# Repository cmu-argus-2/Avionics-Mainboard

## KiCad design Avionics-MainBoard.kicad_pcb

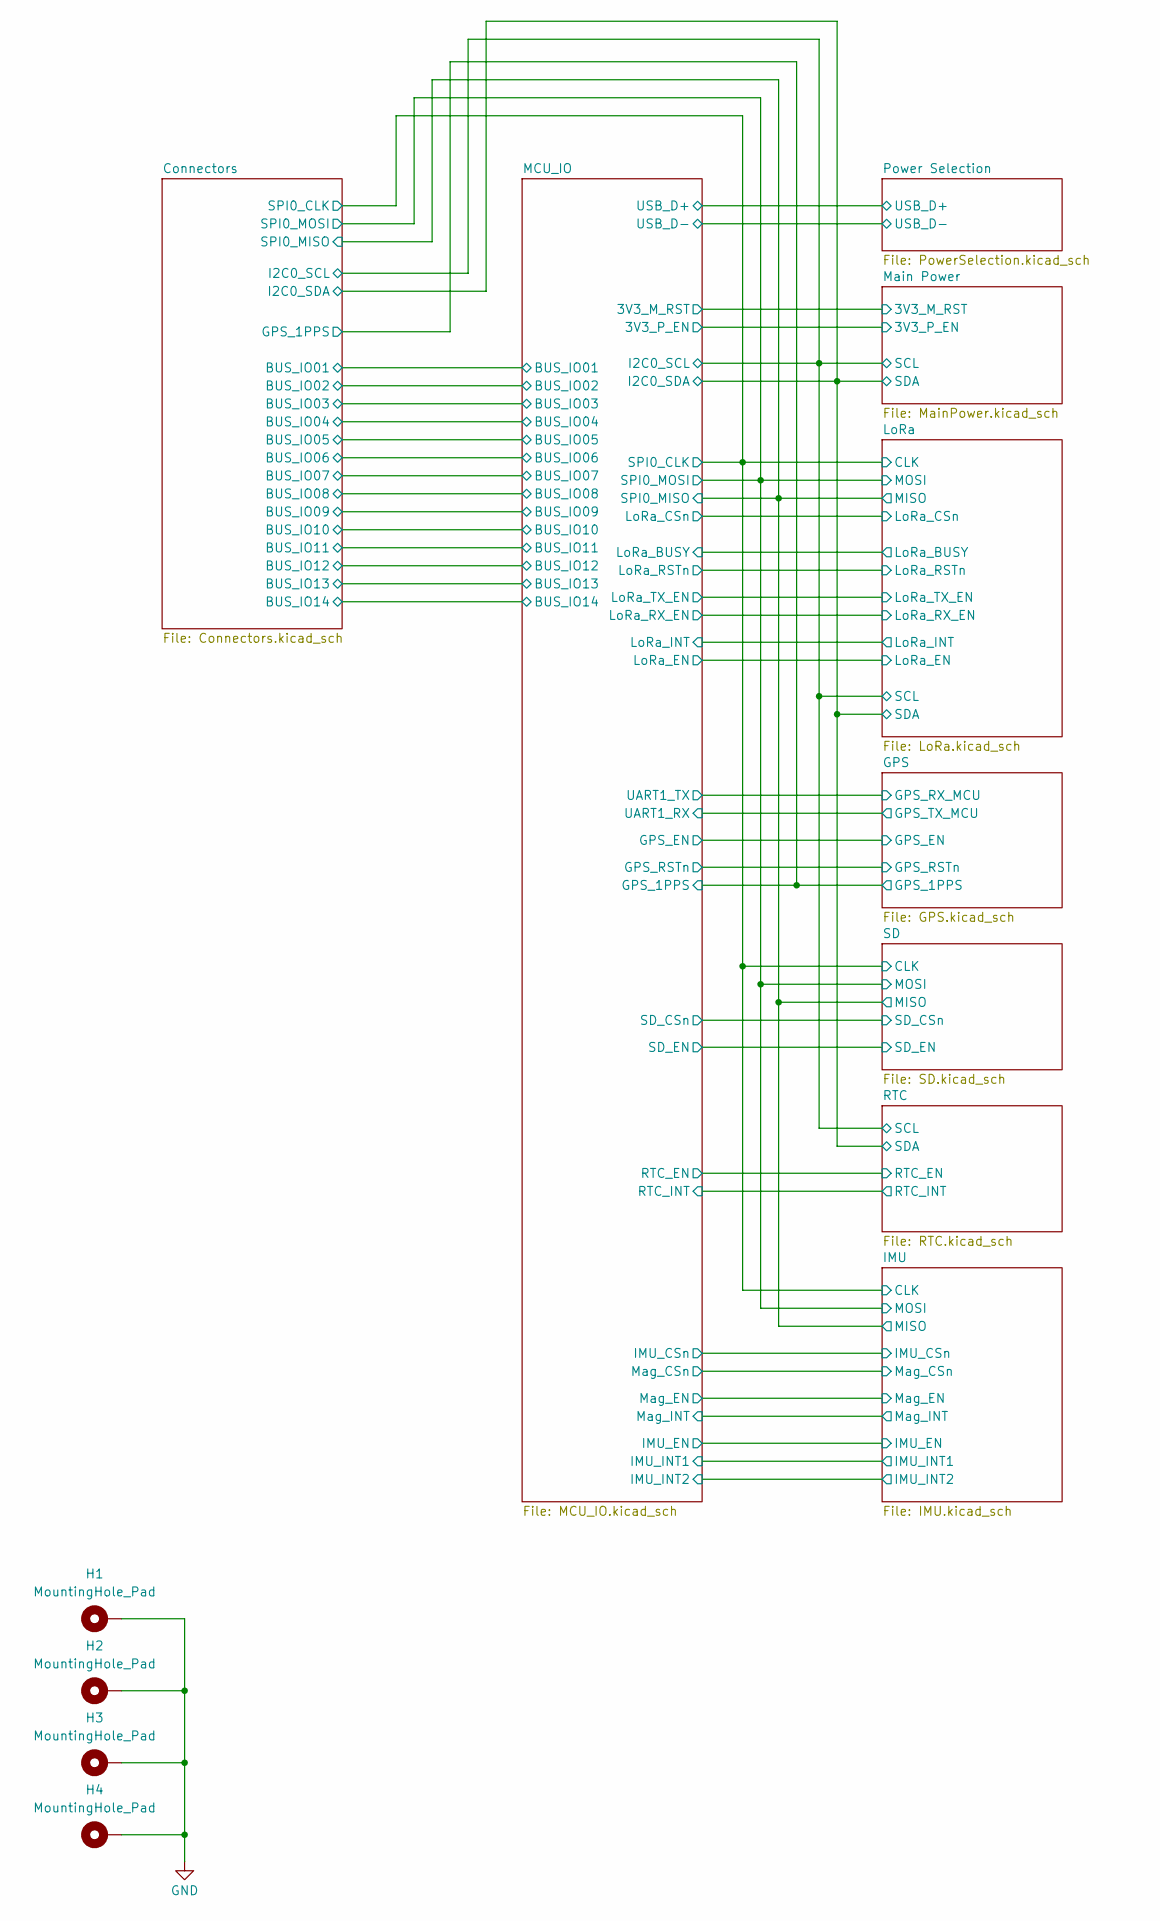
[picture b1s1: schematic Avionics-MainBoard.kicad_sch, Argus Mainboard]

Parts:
H1, H2, H3, H4: MountingHole_Pad; MountingHole_3.2mm_M3_Pad_Via

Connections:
GND: H1.1 (1_1), H2.1 (1_1), H3.1 (1_1), H4.1 (1_1); also elsewhere on the board

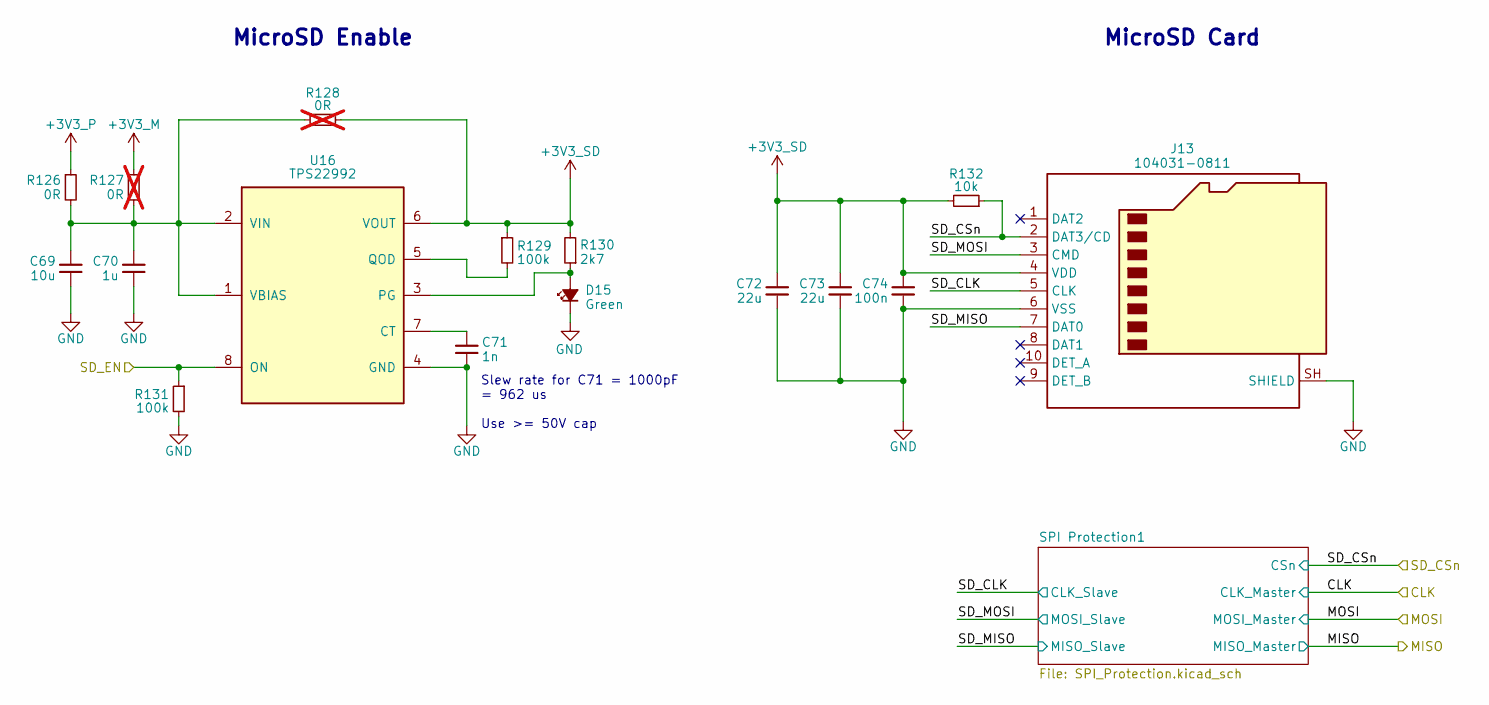
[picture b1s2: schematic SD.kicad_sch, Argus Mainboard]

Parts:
C69: 10u; C_0805_2012Metric; MPN C307348
C70: 1u; C_0603_1608Metric; MPN C307348
C71: 1n; C_0603_1608Metric; MPN C307348
C72, C73: 22u; C_1210_3225Metric
C74: 100n; C_0603_1608Metric; MPN C307348
D15: LED_G_0603_LTST-C190GKT; LED_0603_1608Metric; MPN C2909774
J13: 104031-0811; microSD_HC_Molex_104031-0811; MPN C585350
R126: 0R; R_0603_1608Metric
R127: 0R; R_0603_1608Metric; not fitted
R128: 0R; R_0603_1608Metric; MPN C2479067; not fitted
R129, R131: 100k; R_0603_1608Metric; MPN C2479067
R130: 2k7; R_0603_1608Metric; MPN C237112
R132: 10k; R_0603_1608Metric; MPN C2479067
U16: TPS22992

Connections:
+3V3_M: R127.1; also elsewhere on the board
+3V3_P: R126.1; also elsewhere on the board
+3V3_SD: C72.1, C73.1, C74.1, J13.4 (VDD), R128.1, R129.1, R130.2, R132.2, U16.6 (VOUT)
/MCU_IO/SD_CSn: J13.2 (DAT3/CD), R132.1; also elsewhere on the board
/MCU_IO/SD_EN: R131.1, U16.8 (ON); also elsewhere on the board
/SD/SD_CLK: J13.5 (CLK); also elsewhere on the board
/SD/SD_MISO: J13.7 (DAT0); also elsewhere on the board
/SD/SD_MOSI: J13.3 (CMD); also elsewhere on the board
GND: C69.2, C70.2, C71.2, C72.2, C73.2, C74.2, D15.1 (K), J13.6 (VSS), J13.SH (SHIELD), R131.2, U16.4 (GND); also elsewhere on the board
unnamed: D15.2 (A), R130.1, U16.3 (PG)
unnamed: C71.1, U16.7 (CT)
unnamed: R129.2, U16.5 (QOD)
unnamed: C69.1, C70.1, R126.2, R127.2, R128.2, U16.1 (VBIAS), U16.2 (VIN)

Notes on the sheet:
Slew rate for C71 = 1000pF = 962 us Use >= 50V cap
MicroSD Enable
MicroSD Card

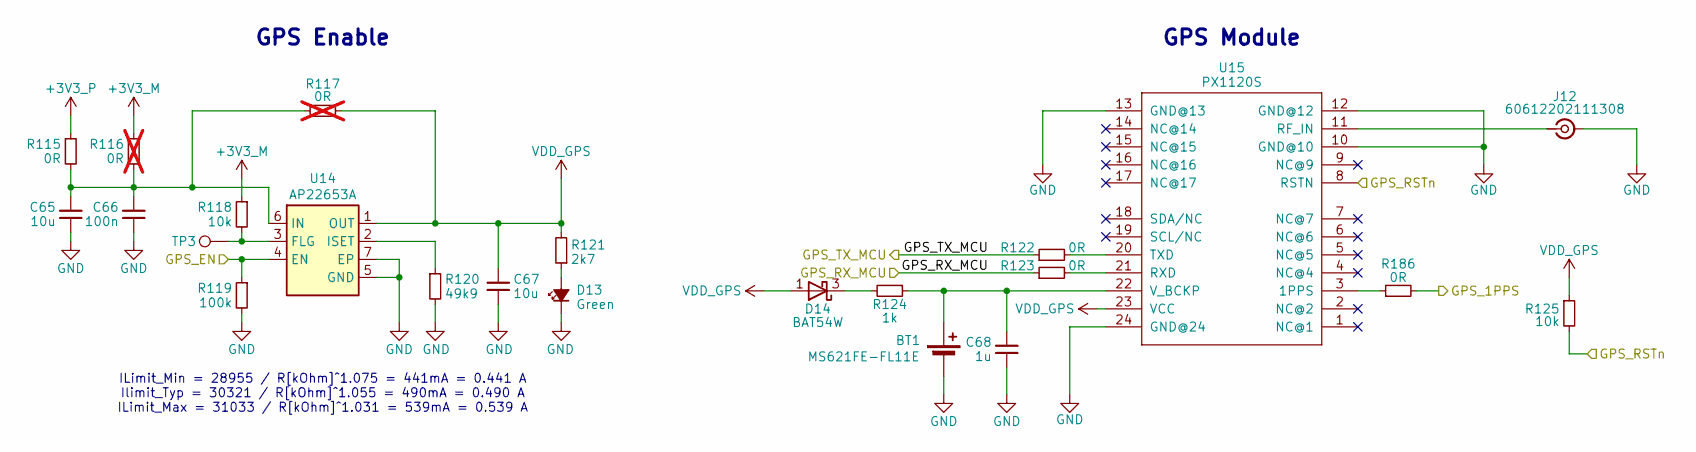
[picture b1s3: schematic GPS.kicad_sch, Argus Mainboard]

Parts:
BT1: MS621FE-FL11E; BatteryHolder_Seiko_MS621F; MPN MS621FE-FL11E
C65, C67: 10u; C_0805_2012Metric; MPN C386084
C66: 100n; C_0603_1608Metric; MPN C307348
C68: 1u; C_0603_1608Metric; MPN C2214844
D13: LED_G_0603_LTST-C190GKT; LED_0603_1608Metric; MPN C2909774
D14: BAT54W; SOT-323_SC-70
J12: 60612202111308; MPN C88374
R115: 0R; R_0603_1608Metric
R116: 0R; R_0603_1608Metric; not fitted
R117: 0R; R_0603_1608Metric; MPN C2479067; not fitted
R118, R125: 10k; R_0603_1608Metric; MPN C2479067
R119: 100k; R_0603_1608Metric; MPN C237792
R120: 49k9; R_0603_1608Metric; MPN C844789
R121: 2k7; R_0603_1608Metric; MPN C237112
R122, R123, R186: 0R; R_0603_1608Metric; MPN C844915
R124: 1k; R_0603_1608Metric; MPN C2076947
TP3: TestPoint; TestPoint_Pad_D1.5mm
U14: AP22653A; DFN-6-1EP_2x2mm_P0.65mm_EP1x1.6mm; MPN C1511768
U15: PX1120S; S1216_24PIN_PACKAGE

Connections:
+3V3_M: R116.1, R118.1; also elsewhere on the board
+3V3_P: R115.1; also elsewhere on the board
/GPS/GPS_RX_MCU: R123.1; also elsewhere on the board
/GPS/GPS_TX_MCU: R122.1; also elsewhere on the board
/MCU_IO/GPS_1PPS: R186.2; also elsewhere on the board
/MCU_IO/GPS_EN: R119.1, U14.4 (EN); also elsewhere on the board
/MCU_IO/GPS_RSTn: R125.2, U15.8 (RSTN); also elsewhere on the board
GND: BT1.2 (-), C65.1, C66.1, C67.1, C68.1, D13.1 (K), J12.2 (Ext), R119.2, R120.2, U14.5 (GND), U14.7 (EP), U15.10 (GND@10), U15.12 (GND@12), U15.13 (GND@13), U15.24 (GND@24); also elsewhere on the board
unnamed: BT1.1 (+), C68.2, R124.1, U15.22 (V_BCKP)
unnamed: D13.2 (A), R121.1
unnamed: D14.3 (K), R124.2
unnamed: J12.1 (In), U15.11 (RF_IN)
unnamed: R118.2, TP3.1 (1_1), U14.3 (FLG)
unnamed: C65.2, C66.2, R115.2, R116.2, R117.2, U14.6 (IN)
unnamed: R120.1, U14.2 (ISET)
unnamed: R186.1, U15.3 (1PPS)
unnamed: R123.2, U15.21 (RXD)
unnamed: R122.2, U15.20 (TXD)
VDD_GPS: C67.2, D14.1 (A), R117.1, R121.2, R125.1, U14.1 (OUT), U15.23 (VCC)

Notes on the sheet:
ILimit_Min = 28955 / R[kOhm]^1.075 = 441mA = 0.441 A Ilimit_Typ = 30321 / R[kOhm]^1.055 = 490mA = 0.490 A ILimit_Max = 31033 / R[kOhm]^1.031 = 539mA = 0.539 A
GPS Enable
GPS Module

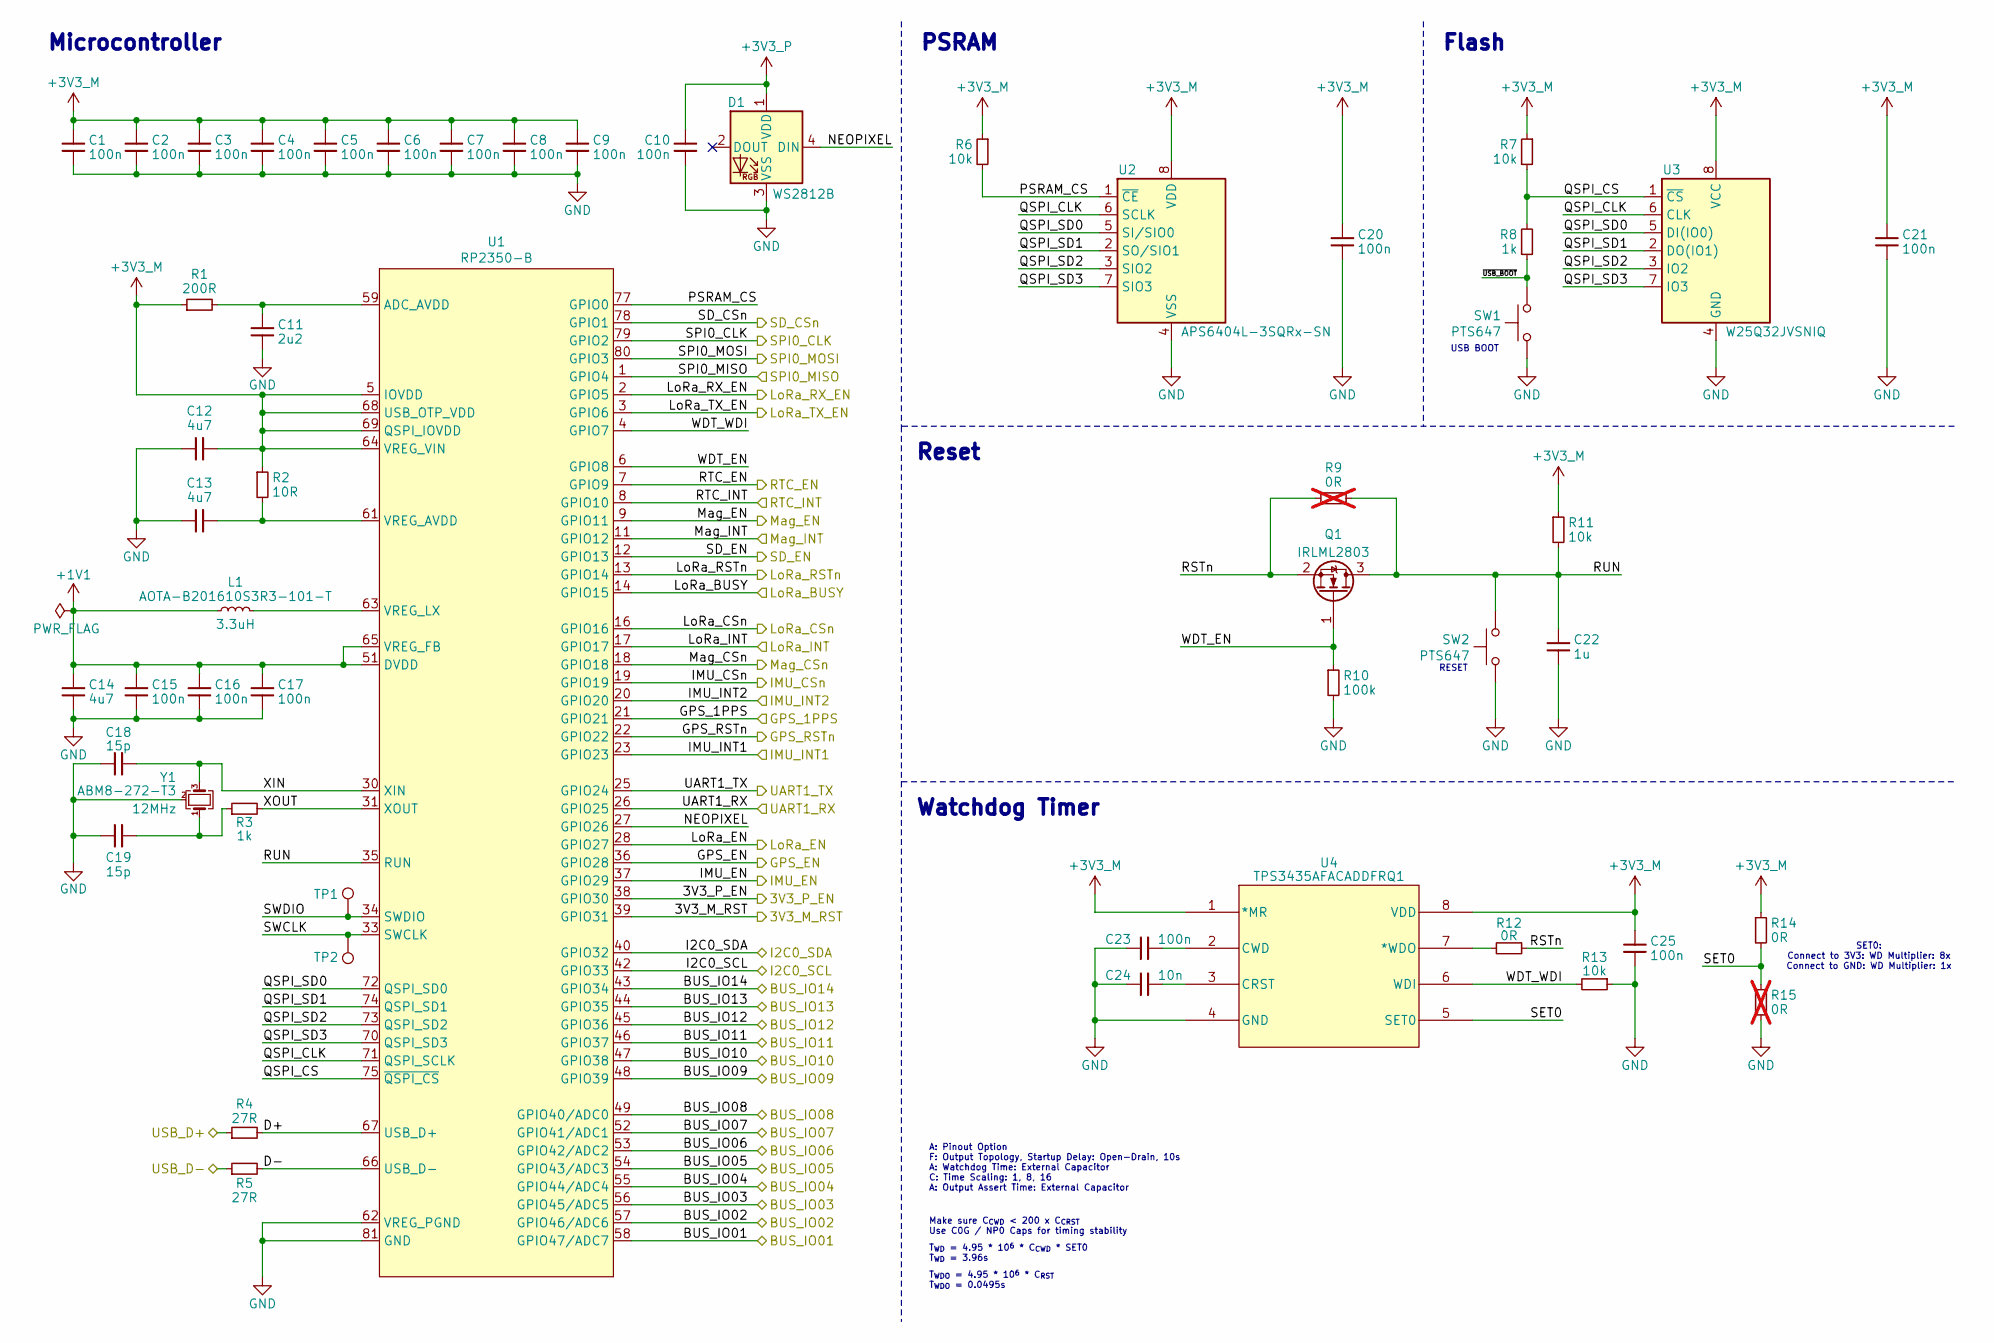
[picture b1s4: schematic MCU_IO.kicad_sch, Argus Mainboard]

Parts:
C1, C2, C3, C4, C5, C6, C7, C8, C9, C10, C15, C16, C17, C20, C21, C25: 100n; C_0603_1608Metric; MPN C307348
C11: 2u2; C_0603_1608Metric; MPN C16193991
C12, C13: 4u7; C_0805_2012Metric; MPN C3861036
C14: 4u7; C_0805_2012Metric; MPN C386084
C18, C19: 15p; C_0603_1608Metric; MPN C346205
C22: 1u; C_0603_1608Metric; MPN C2214844
C23: 100n; C_1210_3225Metric; MPN C307348
C24: 10n; C_0603_1608Metric; MPN C307348
D1: WS2812B; LED_WS2812B_PLCC4_5.0x5.0mm_P3.2mm; MPN C2890040
L1: AOTA-B201610S3R3-101-T; L_0806_2016Metric; MPN C42411119
Q1: IRLML2803; SOT-23; MPN C2590
R1: 200R; R_0603_1608Metric; MPN C844757
R2: 10R; R_0603_1608Metric; MPN C3029194
R3, R8: 1k; R_0603_1608Metric; MPN C2484712
R4, R5: 27R; R_0603_1608Metric; MPN C844545
R6, R7, R11, R13: 10k; R_0603_1608Metric; MPN C2479067
R9: 0R; R_0603_1608Metric; not fitted
R10: 100k; R_0603_1608Metric; MPN C237792
R12: 0R; R_0603_1608Metric; MPN C2479067
R14: 0R; R_0603_1608Metric; MPN C3029194
R15: 0R; R_0603_1608Metric; MPN C3029194; not fitted
SW1, SW2: PTS647; SW_SPST_PTS647_Sx38; MPN C231329
TP1, TP2: TestPoint; TestPoint_Pad_D1.5mm
U1: RP2350-B; RP2350-QFN-80-1EP_10x10_P0.4mm_EP3.4x3.4mm_ThermalVias; MPN C42415655
U2: APS6404L-3SQRx-SN; SOIC-8_3.9x4.9mm_P1.27mm
U3: W25Q32JVSNIQ; DFN-8-1EP_6x5mm_P1.27mm_EP2x2mm
U4: TPS3435AFACADDFRQ1; TSOT-23-8
Y1: ABM8-272-T3; Crystal_SMD_3225-4Pin_3.2x2.5mm; Part 12MHz

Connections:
+1V1: C14.1, C15.1, C16.1, C17.1, L1.1, U1.10 (DVDD), U1.32 (DVDD), U1.51 (DVDD), U1.65 (VREG_FB)
+3V3_M: C1.1, C2.1, C3.1, C4.1, C5.1, C6.1, C7.1, C8.1, C9.1, C12.2, C20.1, C21.1, C25.1, R1.1, R2.1, R6.1, R7.1, R11.1, R14.1, U1.5 (IOVDD), U1.15 (IOVDD), U1.24 (IOVDD), U1.29 (IOVDD), U1.41 (IOVDD), U1.50 (IOVDD), U1.60 (IOVDD), U1.64 (VREG_VIN), U1.68 (USB_OTP_VDD), U1.69 (QSPI_IOVDD), U1.76 (IOVDD), U2.8 (VDD), U3.8 (VCC), U4.1 (*MR), U4.8 (VDD); also elsewhere on the board
+3V3_P: C10.1, D1.1 (VDD); also elsewhere on the board
/GPS/GPS_RX_MCU: U1.25 (GPIO24); also elsewhere on the board
/GPS/GPS_TX_MCU: U1.26 (GPIO25); also elsewhere on the board
/IMU/CLK: U1.79 (GPIO2); also elsewhere on the board
/IMU/IMU_CSn: U1.19 (GPIO19); also elsewhere on the board
/IMU/IMU_INT1: U1.23 (GPIO23); also elsewhere on the board
/IMU/IMU_INT2: U1.20 (GPIO20); also elsewhere on the board
/IMU/MISO: U1.1 (GPIO4); also elsewhere on the board
/IMU/MOSI: U1.80 (GPIO3); also elsewhere on the board
/IMU/Mag_CSn: U1.18 (GPIO18); also elsewhere on the board
/IMU/Mag_INT: U1.11 (GPIO12); also elsewhere on the board
/LoRa/LoRa_BUSY: U1.14 (GPIO15); also elsewhere on the board
/LoRa/LoRa_CSn: U1.16 (GPIO16); also elsewhere on the board
/LoRa/LoRa_INT: U1.17 (GPIO17); also elsewhere on the board
/LoRa/LoRa_RSTn: U1.13 (GPIO14); also elsewhere on the board
/LoRa/LoRa_RX_EN: U1.2 (GPIO5); also elsewhere on the board
/LoRa/LoRa_TX_EN: U1.3 (GPIO6); also elsewhere on the board
/MCU_IO/3V3_M_RST: U1.39 (GPIO31); also elsewhere on the board
/MCU_IO/3V3_P_EN: U1.38 (GPIO30); also elsewhere on the board
/MCU_IO/BUS_IO01: U1.58 (GPIO47/ADC7); also elsewhere on the board
/MCU_IO/BUS_IO02: U1.57 (GPIO46/ADC6); also elsewhere on the board
/MCU_IO/BUS_IO03: U1.56 (GPIO45/ADC5); also elsewhere on the board
/MCU_IO/BUS_IO04: U1.55 (GPIO44/ADC4); also elsewhere on the board
/MCU_IO/BUS_IO05: U1.54 (GPIO43/ADC3); also elsewhere on the board
/MCU_IO/BUS_IO06: U1.53 (GPIO42/ADC2); also elsewhere on the board
/MCU_IO/BUS_IO07: U1.52 (GPIO41/ADC1); also elsewhere on the board
/MCU_IO/BUS_IO08: U1.49 (GPIO40/ADC0); also elsewhere on the board
/MCU_IO/BUS_IO09: U1.48 (GPIO39); also elsewhere on the board
/MCU_IO/BUS_IO10: U1.47 (GPIO38); also elsewhere on the board
/MCU_IO/BUS_IO11: U1.46 (GPIO37); also elsewhere on the board
/MCU_IO/BUS_IO12: U1.45 (GPIO36); also elsewhere on the board
/MCU_IO/BUS_IO13: U1.44 (GPIO35); also elsewhere on the board
/MCU_IO/BUS_IO14: U1.43 (GPIO34); also elsewhere on the board
/MCU_IO/D+: R4.2, U1.67 (USB_D+)
/MCU_IO/D-: R5.2, U1.66 (USB_D-)
/MCU_IO/GPS_1PPS: U1.21 (GPIO21); also elsewhere on the board
/MCU_IO/GPS_EN: U1.36 (GPIO28); also elsewhere on the board
/MCU_IO/GPS_RSTn: U1.22 (GPIO22); also elsewhere on the board
/MCU_IO/I2C0_SCL: U1.42 (GPIO33); also elsewhere on the board
/MCU_IO/I2C0_SDA: U1.40 (GPIO32); also elsewhere on the board
/MCU_IO/IMU_EN: U1.37 (GPIO29); also elsewhere on the board
/MCU_IO/LoRa_EN: U1.28 (GPIO27); also elsewhere on the board
/MCU_IO/Mag_EN: U1.9 (GPIO11); also elsewhere on the board
/MCU_IO/NEOPIXEL: D1.4 (DIN), U1.27 (GPIO26)
/MCU_IO/PSRAM_CS: R6.2, U1.77 (GPIO0), U2.1 (~CE)
/MCU_IO/QSPI_CLK: U1.71 (QSPI_SCLK), U2.6 (SCLK), U3.6 (CLK)
/MCU_IO/QSPI_CS: R7.2, R8.2, U1.75 (~QSPI_CS), U3.1 (~CS)
/MCU_IO/QSPI_SD0: U1.72 (QSPI_SD0), U2.5 (SI/SIO0), U3.5 (DI(IO0))
/MCU_IO/QSPI_SD1: U1.74 (QSPI_SD1), U2.2 (SO/SIO1), U3.2 (DO(IO1))
/MCU_IO/QSPI_SD2: U1.73 (QSPI_SD2), U2.3 (SIO2), U3.3 (IO2)
/MCU_IO/QSPI_SD3: U1.70 (QSPI_SD3), U2.7 (SIO3), U3.7 (IO3)
/MCU_IO/RSTn: Q1.2 (S), R9.1, R12.1
/MCU_IO/RTC_EN: U1.7 (GPIO9); also elsewhere on the board
/MCU_IO/RTC_INT: U1.8 (GPIO10); also elsewhere on the board
/MCU_IO/RUN: C22.1, Q1.3 (D), R9.2, R11.2, SW2.2, U1.35 (RUN)
/MCU_IO/SD_CSn: U1.78 (GPIO1); also elsewhere on the board
/MCU_IO/SD_EN: U1.12 (GPIO13); also elsewhere on the board
/MCU_IO/SET0: R14.2, R15.1, U4.5 (SET0)
/MCU_IO/SWCLK: TP2.1 (1_1), U1.33 (SWCLK)
/MCU_IO/SWDIO: TP1.1 (1_1), U1.34 (SWDIO)
/MCU_IO/WDT_EN: Q1.1 (G), R10.1, U1.6 (GPIO8)
/MCU_IO/WDT_WDI: R13.2, U1.4 (GPIO7), U4.6 (WDI)
/MCU_IO/XIN: C18.2, U1.30 (XIN), Y1.3
/MCU_IO/XOUT: R3.2, U1.31 (XOUT)
/MCU_IO/~USB_BOOT: R8.1, SW1.2
/Power Selection/USB_D+: R4.1; also elsewhere on the board
/Power Selection/USB_D-: R5.1; also elsewhere on the board
GND: C1.2, C2.2, C3.2, C4.2, C5.2, C6.2, C7.2, C8.2, C9.2, C10.2, C11.1, C12.1, C13.2, C14.2, C15.2, C16.2, C17.2, C18.1, C19.2, C20.2, C21.2, C22.2, C23.2, C24.2, C25.2, D1.3 (VSS), R10.2, R13.1, R15.2, SW1.1, SW2.1, U1.62 (VREG_PGND), U1.81 (GND), U2.4 (VSS), U3.4 (GND), U3.9 (GND), U4.4 (GND), Y1.2 (G), Y1.4 (G); also elsewhere on the board
unnamed: C19.1, R3.1, Y1.1
unnamed: C11.2, R1.2, U1.59 (ADC_AVDD)
unnamed: C13.1, R2.2, U1.61 (VREG_AVDD)
unnamed: L1.2, U1.63 (VREG_LX)
unnamed: R12.2, U4.7 (*WDO)
unnamed: C24.1, U4.3 (CRST)
unnamed: C23.1, U4.2 (CWD)

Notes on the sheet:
USB BOOT
Reset
RESET
SET0: Connect to 3V3: WD Multiplier: 8x Connect to GND: WD Multiplier: 1x
T_{WDO} = 4.95 * 10^{6} * C_{RST} T_{WDO} = 0.0495s
Make sure C_{CWD} < 200 x C_{CRST} Use C0G / NP0 Caps for timing stability
T_{WD} = 4.95 * 10^{6} * C_{CWD} * SET0 T_{WD} = 3.96s
Watchdog Timer
PSRAM
Flash
A: Pinout Option F: Output Topology, Startup Delay: Open-Drain, 10s A: Watchdog Time: External Capacitor C: Time Scaling: 1, 8, 16 A: Output Assert Time: External Capacitor
Microcontroller

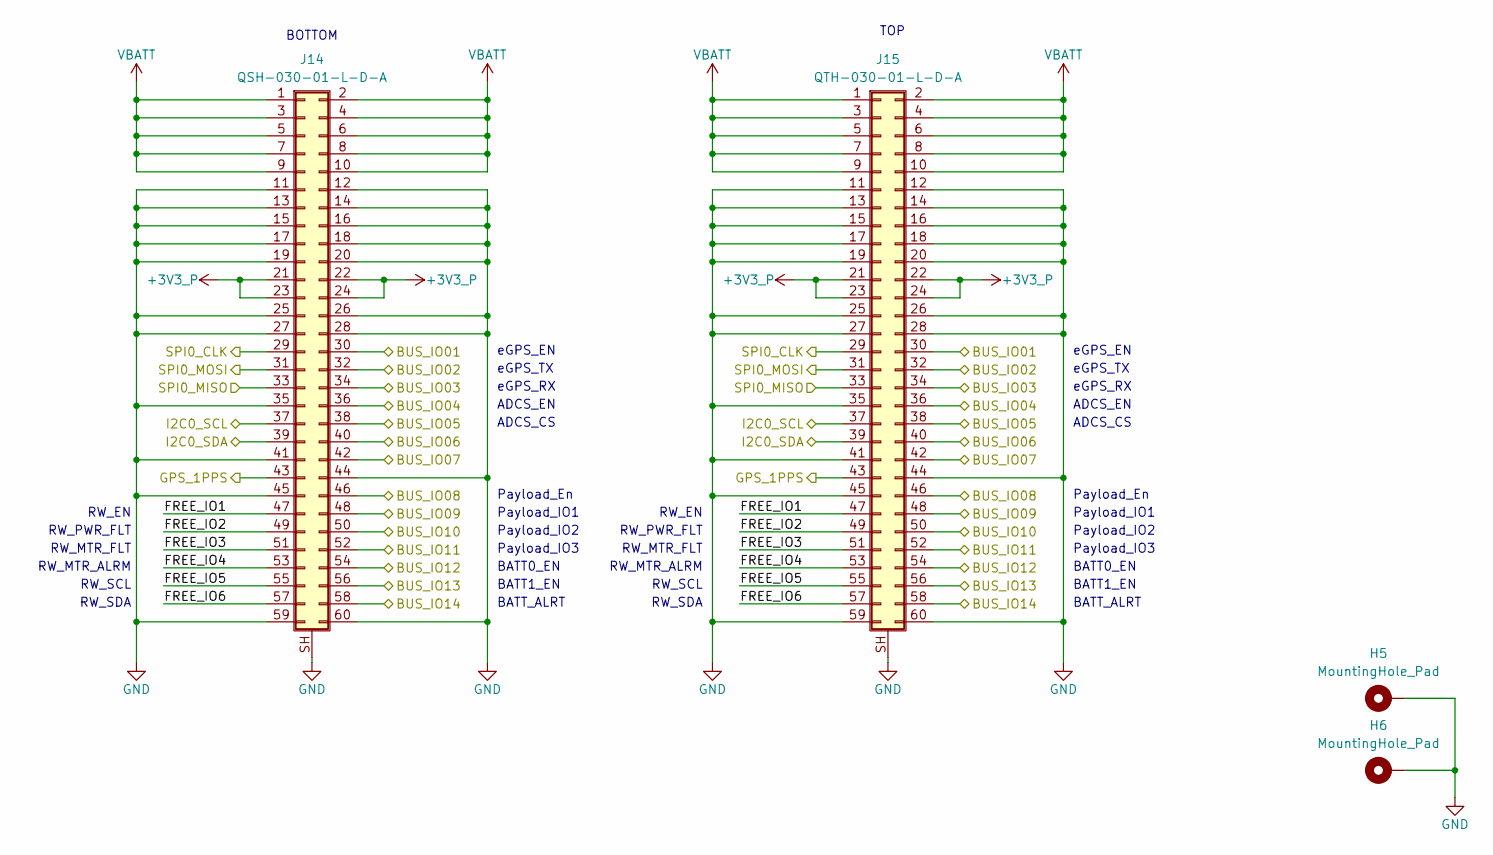
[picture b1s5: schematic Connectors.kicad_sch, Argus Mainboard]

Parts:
H5, H6: MountingHole_Pad; MountingHole_2.7mm_M2.5_Pad_Via
J14: QSH-030-01-L-D-A; SAMTEC_QSH-030-01-L-D-A
J15: QTH-030-01-L-D-A; SAMTEC-QTH-030-01-X-D-A

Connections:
+3V3_P: J14.21, J14.22, J14.23, J14.24, J15.21, J15.22, J15.23, J15.24; also elsewhere on the board
/Connectors/FREE_IO1: J14.47, J15.47
/Connectors/FREE_IO2: J14.49, J15.49
/Connectors/FREE_IO3: J14.51, J15.51
/Connectors/FREE_IO4: J14.53, J15.53
/Connectors/FREE_IO5: J14.55, J15.55
/Connectors/FREE_IO6: J14.57, J15.57
/IMU/CLK: J14.29, J15.29; also elsewhere on the board
/IMU/MISO: J14.33, J15.33; also elsewhere on the board
/IMU/MOSI: J14.31, J15.31; also elsewhere on the board
/MCU_IO/BUS_IO01: J14.30, J15.30; also elsewhere on the board
/MCU_IO/BUS_IO02: J14.32, J15.32; also elsewhere on the board
/MCU_IO/BUS_IO03: J14.34, J15.34; also elsewhere on the board
/MCU_IO/BUS_IO04: J14.36, J15.36; also elsewhere on the board
/MCU_IO/BUS_IO05: J14.38, J15.38; also elsewhere on the board
/MCU_IO/BUS_IO06: J14.40, J15.40; also elsewhere on the board
/MCU_IO/BUS_IO07: J14.42, J15.42; also elsewhere on the board
/MCU_IO/BUS_IO08: J14.46, J15.46; also elsewhere on the board
/MCU_IO/BUS_IO09: J14.48, J15.48; also elsewhere on the board
/MCU_IO/BUS_IO10: J14.50, J15.50; also elsewhere on the board
/MCU_IO/BUS_IO11: J14.52, J15.52; also elsewhere on the board
/MCU_IO/BUS_IO12: J14.54, J15.54; also elsewhere on the board
/MCU_IO/BUS_IO13: J14.56, J15.56; also elsewhere on the board
/MCU_IO/BUS_IO14: J14.58, J15.58; also elsewhere on the board
/MCU_IO/GPS_1PPS: J14.43, J15.43; also elsewhere on the board
/MCU_IO/I2C0_SCL: J14.37, J15.37; also elsewhere on the board
/MCU_IO/I2C0_SDA: J14.39, J15.39; also elsewhere on the board
GND: H5.1 (1_1), H6.1 (1_1), J14.11, J14.12, J14.13, J14.14, J14.15, J14.16, J14.17, J14.18, J14.19, J14.20, J14.25, J14.26, J14.27, J14.28, J14.35, J14.41, J14.44, J14.45, J14.59, J14.60, J14.SH (Shield), J15.11, J15.12, J15.13, J15.14, J15.15, J15.16, J15.17, J15.18, J15.19, J15.20, J15.25, J15.26, J15.27, J15.28, J15.35, J15.41, J15.44, J15.45, J15.59, J15.60, J15.SH (Shield); also elsewhere on the board
VBATT: J14.1, J14.2, J14.3, J14.4, J14.5, J14.6, J14.7, J14.8, J14.9, J14.10, J15.1, J15.2, J15.3, J15.4, J15.5, J15.6, J15.7, J15.8, J15.9, J15.10; also elsewhere on the board

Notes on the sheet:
BATT1_EN
RW_SCL
RW_PWR_FLT
Payload_IO1
Payload_En
RW_EN
eGPS_TX
eGPS_EN
eGPS_RX
BATT_ALRT
RW_MTR_FLT
ADCS_CS
RW_MTR_ALRM
Payload_IO3
BOTTOM
BATT0_EN
RW_SDA
ADCS_EN
Payload_IO2
TOP

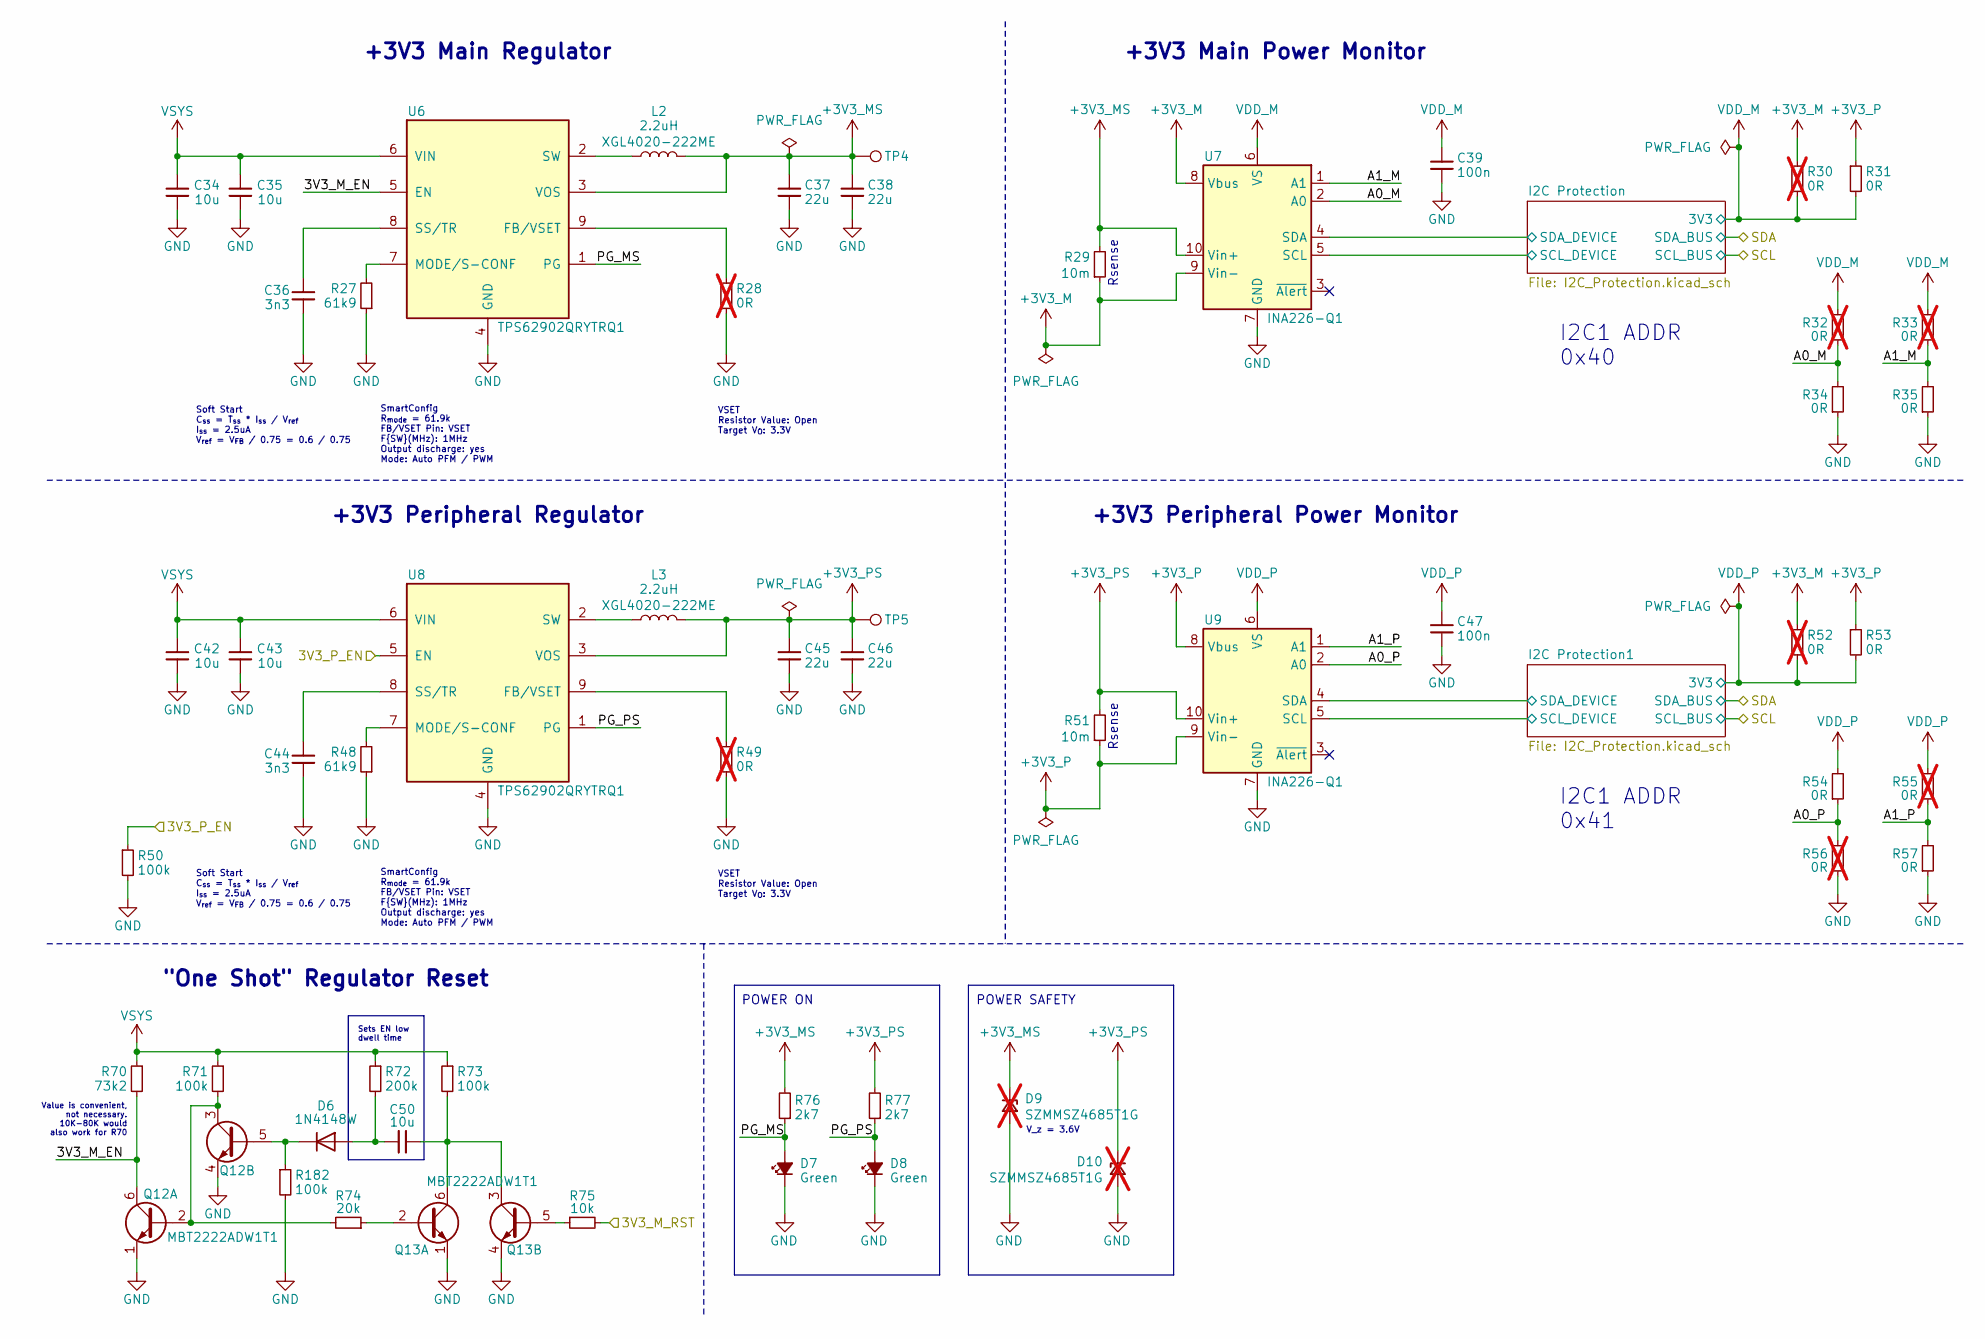
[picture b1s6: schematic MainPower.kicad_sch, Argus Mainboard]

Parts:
C34, C35, C42, C43, C50: 10u; C_0805_2012Metric; MPN C386084
C36, C44: 3n3; C_0603_1608Metric; MPN C3877267
C37, C38, C45, C46: 22u; C_1210_3225Metric; MPN C2803395
C39, C47: 100n; C_0603_1608Metric; MPN C2803395
D6: 1N4148W; D_SOD-123
D7, D8: LED_G_0603_LTST-C190GKT; LED_0603_1608Metric; MPN C2909774
D9, D10: SZMMSZ4685T1G; D_SOD-123; not fitted
L2, L3: 2.2uH; L_Coilcraft_XAL4020-XXX
Q12: MBT2222ADW1T1; SOT-363_SC-70-6
Q13: MBT2222ADW1T1; SOT-363_SC-70-6; Manufacturer_Part_Number MBT2222ADW1T1G
R27, R48: 61k9; R_0603_1608Metric; MPN C844759
R28, R49: 0R; R_0603_1608Metric; MPN C844759; not fitted
R29, R51: 10m; R_1206_3216Metric; MPN C840621
R30, R52: 0R; R_0603_1608Metric; MPN C237792; not fitted
R31, R53: 0R; R_0603_1608Metric; MPN C237792
R32, R33, R55, R56: 0R; R_0603_1608Metric; MPN C844915; not fitted
R34, R35, R54, R57: 0R; R_0603_1608Metric; MPN C844915
R50, R71, R73, R182: 100k; R_0603_1608Metric; MPN C237792
R70: 73k2; R_0603_1608Metric; MPN C843966
R72: 200k; R_0603_1608Metric; MPN C118142
R74: 20k; R_0603_1608Metric; MPN C844923
R75: 10k; R_0603_1608Metric; MPN C2479067
R76, R77: 2k7; R_0603_1608Metric; MPN C237112
TP4, TP5: TestPoint; TestPoint_Pad_D1.5mm
U6, U8: TPS62902QRYTRQ1
U7, U9: INA226-Q1; TSSOP-10_3x3mm_P0.5mm

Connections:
+3V3_M: R29.1, R30.1, R52.1, U7.8 (Vbus), U7.9 (Vin-); also elsewhere on the board
+3V3_MS: C37.2, C38.2, D9.1 (K), L2.2, R29.2, R76.2, TP4.1 (1_1), U6.3 (VOS), U7.10 (Vin+)
+3V3_P: R31.1, R51.1, R53.1, U9.8 (Vbus), U9.9 (Vin-); also elsewhere on the board
+3V3_PS: C45.2, C46.2, D10.1 (K), L3.2, R51.2, R77.2, TP5.1 (1_1), U8.3 (VOS), U9.10 (Vin+)
/MCU_IO/3V3_M_RST: R75.2; also elsewhere on the board
/MCU_IO/3V3_P_EN: R50.1, U8.5 (EN); also elsewhere on the board
/Main Power/3V3_M_EN: Q12.6 (C1), R70.2, U6.5 (EN)
/Main Power/A0_M: R32.1, R34.2, U7.2 (A0)
/Main Power/A0_P: R54.1, R56.2, U9.2 (A0)
/Main Power/A1_M: R33.1, R35.2, U7.1 (A1)
/Main Power/A1_P: R55.1, R57.2, U9.1 (A1)
/Main Power/I2C Protection1/SCL_DEVICE: U9.5 (SCL); also elsewhere on the board
/Main Power/I2C Protection1/SDA_DEVICE: U9.4 (SDA); also elsewhere on the board
/Main Power/I2C Protection/SCL_DEVICE: U7.5 (SCL); also elsewhere on the board
/Main Power/I2C Protection/SDA_DEVICE: U7.4 (SDA); also elsewhere on the board
/Main Power/PG_MS: D7.2 (A), R76.1, U6.1 (PG)
/Main Power/PG_PS: D8.2 (A), R77.1, U8.1 (PG)
GND: C34.2, C35.2, C36.1, C37.1, C38.1, C39.1, C42.2, C43.2, C44.1, C45.1, C46.1, C47.1, D7.1 (K), D8.1 (K), D9.2 (A), D10.2 (A), Q12.1 (E1), Q12.4 (E2), Q13.1 (E1), Q13.4 (E2), R27.1, R28.1, R34.1, R35.1, R48.1, R49.1, R50.2, R56.1, R57.1, R182.2, U6.4 (GND), U7.7 (GND), U8.4 (GND), U9.7 (GND); also elsewhere on the board
unnamed: C50.2, D6.2 (A), R72.2
unnamed: D6.1 (K), Q12.5 (B2), R182.1
unnamed: Q12.2 (B1), Q12.3 (C2), R71.2, R74.2
unnamed: Q13.2 (B1), R74.1
unnamed: C50.1, Q13.3 (C2), Q13.6 (C1), R73.2
unnamed: Q13.5 (B2), R75.1
unnamed: R28.2, U6.9 (FB/VSET)
unnamed: R27.2, U6.7 (MODE/S-CONF)
unnamed: C36.2, U6.8 (SS/TR)
unnamed: L2.1, U6.2 (SW)
unnamed: R49.2, U8.9 (FB/VSET)
unnamed: R48.2, U8.7 (MODE/S-CONF)
unnamed: C44.2, U8.8 (SS/TR)
unnamed: L3.1, U8.2 (SW)
VDD_M: C39.2, R30.2, R31.2, R32.2, R33.2, U7.6 (VS); also elsewhere on the board
VDD_P: C47.2, R52.2, R53.2, R54.2, R55.2, U9.6 (VS); also elsewhere on the board
VSYS: C34.1, C35.1, C42.1, C43.1, R70.1, R71.1, R72.1, R73.1, U6.6 (VIN), U8.6 (VIN); also elsewhere on the board

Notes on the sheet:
Rsense
VSET Resistor Value: Open Target V_{O}: 3.3V
Sets EN low dwell time
V_z = 3.6V
I2C1 ADDR 0x41
SmartConfig R_{mode} = 61.9k FB/VSET Pin: VSET F{SW}(MHz): 1MHz Output discharge: yes Mode: Auto PFM / PWM
Value is convenient, not necessary. 10K-80K would also work for R70
Soft Start C_{ss} = T_{ss} * I_{ss} / V_{ref} I_{ss} = 2.5uA V_{ref} = V_{FB} / 0.75 = 0.6 / 0.75
+3V3 Main Regulator
"One Shot" Regulator Reset
+3V3 Peripheral Power Monitor
I2C1 ADDR 0x40
+3V3 Peripheral Regulator
POWER SAFETY
+3V3 Main Power Monitor
POWER ON

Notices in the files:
parts and their libraries:
License: Apache-2.0
